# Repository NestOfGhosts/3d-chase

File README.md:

# 3d-chase
3d cube of led's as interface for simple game of snake without the body of the snake. Made by me for Hack Club Half Life.

Dear hack club reviewer. You may notice that most of the images are absolute garbage. Most are placeholders for when i do the project personally, and when I do ill add better images and remove this comment

## Premise

3d led cube:

But it's snake:

But the cube is 9x9x9 so i dont think the snake's body would work, so it's just going to be a led moving towards blinking leds.

### The game explaination
These are what the keys map to.

PWR just start the game, and does nothing beyond that. Why is it called PWR? Because I thought i was going to do more with the button. The other keys that move you along the x,y, and z axis.

You start in (0,0,0(Corner of the cube)) as the lit up led, and the goal starts in (1,1,1 (center of the cube)) as the blinking led. 
You have 3.5 seconds to move your light to the goal. A new goal will spawn, and every 3 points the time limit will go down. 

Here are the values for every time decrease (in milliseconds): 3500, 2940, 2505, 2168, 1907, 1703, 1546, 1424, 1329, 1255, 1198, 1154, 1119, 1093, 1072, 1056, 1043, 1034, 1026, 1020, 1016, 1012, 1009, 1007, 1006, 1005, 1004, 1003, 1002, 1001, 1000.

Past 90 points, the time stays at a static 1000 milliseconds (1 second). You effectively win if you can get to the points within 1 second without making a mistake. If you get to that level, you can try editing the firmware to have a different/steeper decrease slope.

If you move into a wall you fail.

### Additional Note
If you keep it plugged in it will go into a standby mode, where it'll randomly turn on the cubes leds until the cube is filled, then it'll clear it. Lets the cube work as simple decoration.

## Stuff you need

[BOM.csv](https://github.com/NestOfGhosts/3d-chase/blob/main/BOM.csv) is just a copy of the things I personally had to buy for the project and their prices, not a complete list of things you need. The following table is the complete parts list.

|Thing you need|What you need it for|
|--------------|--------------------|
|Soldering equipment and expertise|A simple soldering iron and through-hole skills needed|
|[The Pcb](https://github.com/NestOfGhosts/3d-chase/tree/main/Pcb%20Files)|To hold everything together|
|[The Chassis](https://github.com/NestOfGhosts/3d-chase/tree/main/Chassis%20Files)|To hold everything together but in like a different way :3|
|Arduino Nano Atmega328 with usb c|Just kinda get some clone or something that seems legit enough and compatible/same pin layout as og nano. I got mine from [Aliexpress](https://www.aliexpress.com/item/1005006128051481.html?spm=a2g0o.productlist.0.0.1b334a261XQdtX&mp=1&pdp_npi=6%40dis%21CAD%21CAD+2.74%21CAD+2.74%21%21CAD+2.74%21%21%21%4021032e4e17933253312398755e0fb7%2112000035881712636%21ct%21CA%216330886401%21%211%210%21)|
|7 switches and keycaps|For the controls. Make sure they're mx compatible and 5 pin. MAKE SURE THEY'RE 5 PIN|
|27 Diode leds|The ones with only an anode and cathode, in any colour of your choosing. Im using flattop whites|
|3 Mosfets|Allows you to open and close electrical paths|
|9 ~130-330 ohm resistors|To limit electric flow going to leds. Higher number is more resistant = duller leds. Recommended ohm value is for white leds|
|3 4.7k-100k ohm resistors|Closes electrical path if mosfet isnt *fully* off|
|M4 screws and nuts|To hold the chassis together|
|Wires|I'm using some spare jumpers. Make sure you can connect points at ~20mm, ~40mm, ~60mm. (120mm of wires)|

### Additional notes: 
  - I got my pcb and chassis from JLCPCB and JLC3DP (respectively).
  - The pcb is fully designed for through hole parts
  - Flat topped, diffused leds work better for this projects, because realistically you're looking at the leds from multiple angles and you will be looking at them for periods of time (diffused spreads light out and reduces sharpness). However, diffused leds are expensive, so you can sand the led lightly with a high grit sandpaper (400-1000). Higher is less diffused.
  - Colour of leds correspond to resistor strengths. If you want a different led colour google "____ led resistor ohm"
  - The screws are ISO7380 M4. You may need to edit chassis screw holes if the screws you buy are bigger
  - The firmware is built for the old Atmega328 bootloader. If you want to change it you need to copy the firmware folder, open it in [VS Code](https://code.visualstudio.com), and download [Platformio](https://platformio.org/) (you can also find this in vscode's built in extension store). Then, in the platformio.ini folder change from REMEMBER TO CHANGE THIS
  - The resistor value is are for white leds. You can use [All About Circuits Led Resistor Calculators](https://www.allaboutcircuits.com/tools/led-resistor-calculator/) to calculate it. Aim for about roughly 10-20ma~? It really depends on every Led though so the value is a broad number. You can look at the listing for max ma, and maybe do a couple underneath that.

## Assembly
### Firmware
Instructions are windows
1. Download firmware .hex from [the firmware folder](https://github.com/NestOfGhosts/3d-chase/blob/main/FIrmware/firmware.hex) 
2. Download a .hex firmware flasher [Avrdude](https://blog.zakkemble.net/avrdudess-a-gui-for-avrdude/)
3. Open device manager, and expand the "Ports (COM & LPT)"
4. Plug in the nano. A new port should appear. Take note of the COM number (etcetcetc (COM___))
5. In Avrdude, set preset to "Arduino Nano (Atmega328p)". You may have purchased a Nano with a Atmega328 or Atmega328PB MCU. If so, change MCU to the correct one.

6. In Avrdude, set port to the COM number. Other programmer setting should be correct because of the preset.

7. Add the path to the .hex in the "Flash" field. Set it to "Write", and press "Go"
8. Wait until the terminal at the bottom of the gui says "Success" or smth

### Soldering
Hopefully you have a fume extractor, or have accepted asthma and metals in your lungs
1. Solder the Nano, MOSFETS, and resistors on the backside.
2. Solder switches on frontside.
#### The led cube
3. (Optional): Sand your leds if you more diffusion
4. Bend the cathodes(shorter side) of the leds 90 degrees, with a 1-3mm gap between the bottom of the led and the start of the bend
5. Lay out the leds in a 3x3 grid. Match it up with the hole distances in the pcb (all 2 leds are seperated by 15mm). Make a second bend on the horizontal plane to make each distance between leds 15mm.

(PLACEHOLDER IMAGE)

6. Connect the anodes(longer side) up and down. Make the distance between the layers 15mm to make C U B E.

(PLACEHOLDER IMAGE)

7. Get the wires. Make sure both ends are stripped/open/metal. Now solder one end of the wire on one of the three holes to the left of the pcb (pins labeled L1, L2, L3). IMPORTANT: Wire the bottom most layer to L1, top layer to L3 etc

8. Grab the chassis cover, and route the wires through the holes in the cover.
INSERT IMAGE
9. Solder the wires to the 3x3 layers, and solder the anode columns to the pcb
10. Put the chassis together

## Customizing the firmware.
You need to know c++ to do major changes, because platformio uses c++, but I will go through some simple changes if you dont know C++
- Install [Platformio](https://platformio.org/) on [VS Code](https://code.visualstudio.com)
- Download the [3d Chase Folder](https://github.com/NestOfGhosts/3d-chase/tree/main/FIrmware/3d%20Chase%20Firmware) by pasting the url into [Download Github directory](https://download-directory.github.io/)
- Extract the download
- To open the platformio project, follow the first *commenter*'s instructions in [this forum post](https://community.platformio.org/t/guidance-for-a-platform-io-noob/47188) on how to open platformio projects.
- Now, in src, you can find the main.cpp folder. Top of the file has some simple settings like debounce(how long a button has to be held to be considered pressed), how long the goal's blinks are, and how long one frame of the standby's animation is. On line 86, you can also find the time limit curve. If you dont know c++, i recommend maintaining the timeTable at 31 values, but you can adjust the indivisual values, like making the curve go down faster and end at 500, if you want a challenge. If you want a smoother curve than just guessing values you can use a graphing calculator and your favourite function to create your own curve. 

## Arduino Pins, for the nerds:
D0 = Power button
D1, D2, D3, D4, D5, D6 = X+, X-, Y+, Y-, Z+, Z-
D7, D8, D9 = MOS1, MOS2, MOS3
D10, D11, D12, D13, D14, D15, D16, D17, D18 = Column 1, 2, 3, 4, 5, 6, 7, 8, 9

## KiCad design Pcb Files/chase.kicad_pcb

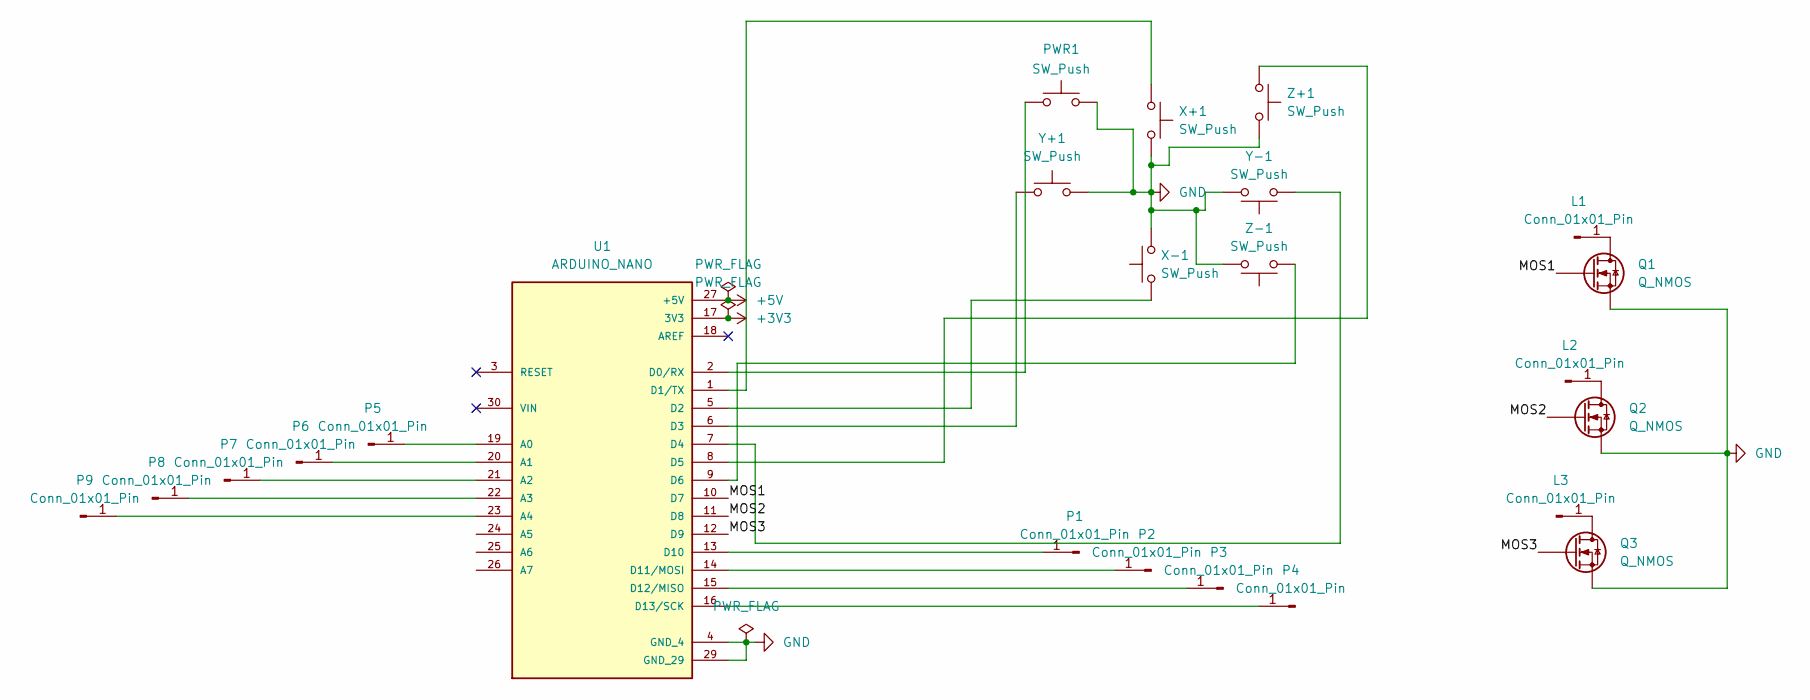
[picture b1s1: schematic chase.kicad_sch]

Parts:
L1, L2, L3: Conn_01x01_Pin; SolderWire-0.5sqmm_1x01_D0.9mm_OD2.1mm
P1, P2, P3, P4, P5, P6, P7, P8, P9: Conn_01x01_Pin; SolderWire-0.5sqmm_1x01_D0.9mm_OD2.1mm
PWR1: SW_Push; SW_Cherry_MX_1.00u_PCB
Q1, Q2, Q3: Q_NMOS; 1x3 1mm diameter through holes
U1: ARDUINO_NANO; Arduino_Nano; PARTREV 30/06/2021
X+1: SW_Push; SW_Cherry_MX_1.00u_PCB
X-1: SW_Push; SW_Cherry_MX_1.00u_PCB
Y+1: SW_Push; SW_Cherry_MX_1.00u_PCB
Y-1: SW_Push; SW_Cherry_MX_1.00u_PCB
Z+1: SW_Push; SW_Cherry_MX_1.00u_PCB
Z-1: SW_Push; SW_Cherry_MX_1.00u_PCB

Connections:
+3V3: U1.17 (3V3)
+5V: U1.27 (+5V)
/MOS1: Q1.G, U1.10 (D7)
/MOS2: Q2.G, U1.11 (D8)
/MOS3: Q3.G, U1.12 (D9)
GND: PWR1.2, Q1.S, Q2.S, Q3.S, U1.4 (GND_4), U1.29 (GND_29), X+1.2, X-1.2, Y+1.2, Y-1.2, Z+1.2, Z-1.2
unnamed: L1.1 (Pin_1_1), Q1.D
unnamed: L2.1 (Pin_1_1), Q2.D
unnamed: L3.1 (Pin_1_1), Q3.D
unnamed: P1.1 (Pin_1_1), U1.13 (D10)
unnamed: P2.1 (Pin_1_1), U1.14 (D11/MOSI)
unnamed: P3.1 (Pin_1_1), U1.15 (D12/MISO)
unnamed: P4.1 (Pin_1_1), U1.16 (D13/SCK)
unnamed: P5.1 (Pin_1_1), U1.19 (A0)
unnamed: P6.1 (Pin_1_1), U1.20 (A1)
unnamed: P7.1 (Pin_1_1), U1.21 (A2)
unnamed: P8.1 (Pin_1_1), U1.22 (A3)
unnamed: P9.1 (Pin_1_1), U1.23 (A4)
unnamed: PWR1.1, U1.2 (D0/RX)
unnamed: U1.1 (D1/TX), X+1.1
unnamed: U1.5 (D2), X-1.1
unnamed: U1.6 (D3), Y+1.1
unnamed: U1.7 (D4), Y-1.1
unnamed: U1.8 (D5), Z+1.1
unnamed: U1.9 (D6), Z-1.1

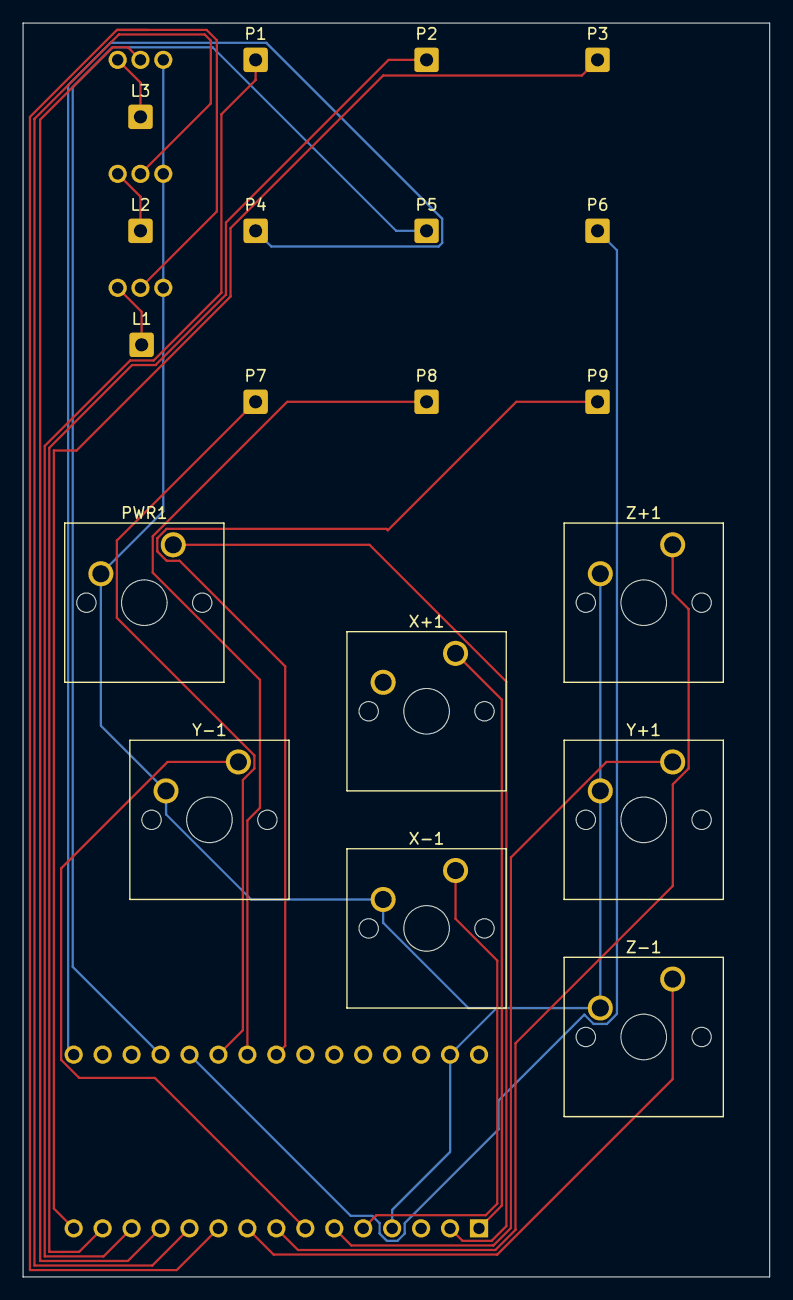
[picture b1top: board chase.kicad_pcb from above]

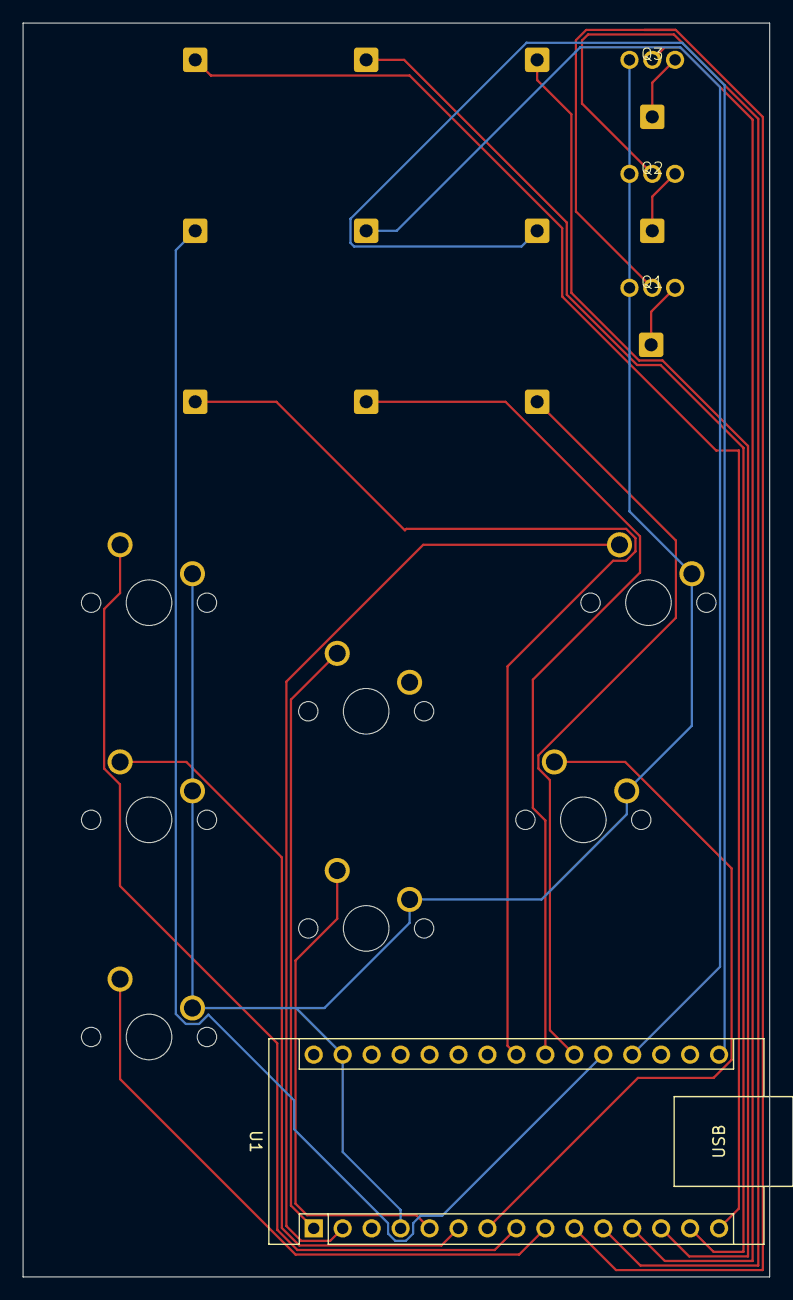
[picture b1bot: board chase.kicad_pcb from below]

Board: 2 copper layers, 65.5 x 110.0 mm, 23 parts (4 on the bottom side), 23 nets.
